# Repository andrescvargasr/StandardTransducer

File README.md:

# StandardTransducer

This repository is dedicated to the v0.2 of Standard Transducer.

## Electronics

The architecture for v0.2 is articulated around one central board powered by an ATmega32u4 MCU relying on ChibiOS/Nil RTOS with LoRa communication and external boards for interfacing to extra sensors, OLED screens and Bluetooth.

The main board comes with the following features:

- 4 ports for digital sensors under 1-wire communication protocol.

- 7 ports for 2 analog sensors with current source or voltage source and differential or single out (this ports was based in pressure sensor MPX53D and temperature sensor PT100).

- 1 port for OLED I2C screen.
- 1 port for 3.7 V battery source or 5 - 12 Vdc @ 1 A.
- 1 port for antenna extension (433 and 868 MHz).
- 1 port for test power source (Vcc).
- 1 port for change power source 3.3 Vdc / 5-12 Vdc.
- 1 port for 868 MHz antenna with SMA connector.
- 1 port for 868 MHz antenna with U.fl connector.
- 1 port for serial Bluetooth.
- 4 buttons for local configuration.
- 1 pad for soldering LoRa Ra-1 (do not include if RN2483 is part of the design).
- 1 pad for soldering LoRa RN2483 (do not include if Ra-01 is part of the design).

There are already a few external extra modules:

~~- OLED I2C slave.~~

~~- pH & Conductommetry regulation I2C slave, also works as a stand alone (in development phase)~~
~~

~~- Pressure analog sensor.~~

~~- Temperature analog sensor.~~

~~- gas flux and mix control with analogic valves, also works as a stand alone (in development phase).~~

References:

-https://www.arduino.cc/en/Main/ArduinoBoardLeonardo.

-https://github.com/greiman/ChNil.

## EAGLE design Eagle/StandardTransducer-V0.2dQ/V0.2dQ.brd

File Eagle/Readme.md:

The main board comes with the following features:

- 3 pads with 3 ports for digital sensors under 1-wire communication protocol.

Port | Name | Description
---|----|---------------------------------------------------------------------------------
1 | Vsensors | Digital Voltage source for one-wire sensors.
2 | One-wire | Digital output of sensors.
3 | GND | Ground for digital sensors.

- 1 connector with 2x5 ports for 2 analog sensors with current source or voltage source, differential or single out (this ports was based in pressure sensor MPX53D and temperature sensor PT100) and one-wire sensors.

Port | Name | Sensor Number | Description
---|----|-------------------------------|---------------------------------------------------------------------------------
1 | D+3V3 |  | Voltage source for sensor 1.
2 | AGND |  | Analog ground for sensor 1 and voltage source.
3 | Vout+ | 1 | Positive differential voltage output of sensor 1.
4 | Vout- | 1 | Negative Differential voltage output of sensor 1.
5 | Iexc |  | Current source for sensor 2.
6 | AGND |  | Analog ground for sensor 2 and current source.
7 | Vanalog | 2 | Analog voltage output of sensor 2.
8 | GND |  | Ground for different digital sensors connect in sensor 3.
9 | Vsensors | | Digital Voltage source for one-wire sensors.
10 | One-wire | 3 | Digital output of sensors in port 10.

- 1 connector with 4 ports for OLED I2C screen.

Port | Name | Description
---|----|---------------------------------------------------------------------------------
1 | SDA | Serial Data.
2 | SCL | Serial Clock.
3 | LCDVCC | Voltage source.
4 | GND | Ground.

- 1 connector with 3 ports for 3.7 V battery source or 5 - 12 Vdc @ 1 A.

Port | Name | Description
---|----|---------------------------------------------------------------------------------
1 | Vdd | 5 - 12 V @ 1 A voltage source.
2 | +3V3 | Battery source.
3 | GND | Ground.

- 1 port for antenna extension (433 and 868 MHz).
- 1 port for test power source (Vcc).
- 1 jumper for change power source 3.3 Vdc to 5-12 Vdc.
- 1 port for 868 MHz antenna with SMA connector.
- 1 port for 868 MHz antenna with U.fl connector.
- 1 connector with 4 ports for serial Bluetooth.

Port | Name | Description
---|----|---------------------------------------------------------------------------------
1 | D+3V3 | Voltage source.
2 | TX2 | Transmission port for slave.
3 | RX2 | Reception port for slave.
4 | GND | Ground.

- 4 buttons for local configuration.
- 1 pad for soldering LoRa Ra-1 (do not include if RN2483 is part of the design).
- 1 pad for soldering LoRa RN2483 (do not include if Ra-01 is part of the design).

References:

- https://www.luisllamas.es/temperatura-liquidos-arduino-ds18b20/
- https://www.nxp.com/docs/en/data-sheet/MPX53.pdf
- https://www.acromag.com/sites/default/files/RTD_Temperature_Measurement_917A.pdf
- https://learn.adafruit.com/monochrome-oled-breakouts
- https://hetpro-store.com/TUTORIALES/bluetooth-hc-06-app-arduino/
- http://www.abatek.com/designguide/04Electrical.html
- https://www.arduino.cc/en/Main/ArduinoBoardLeonardo

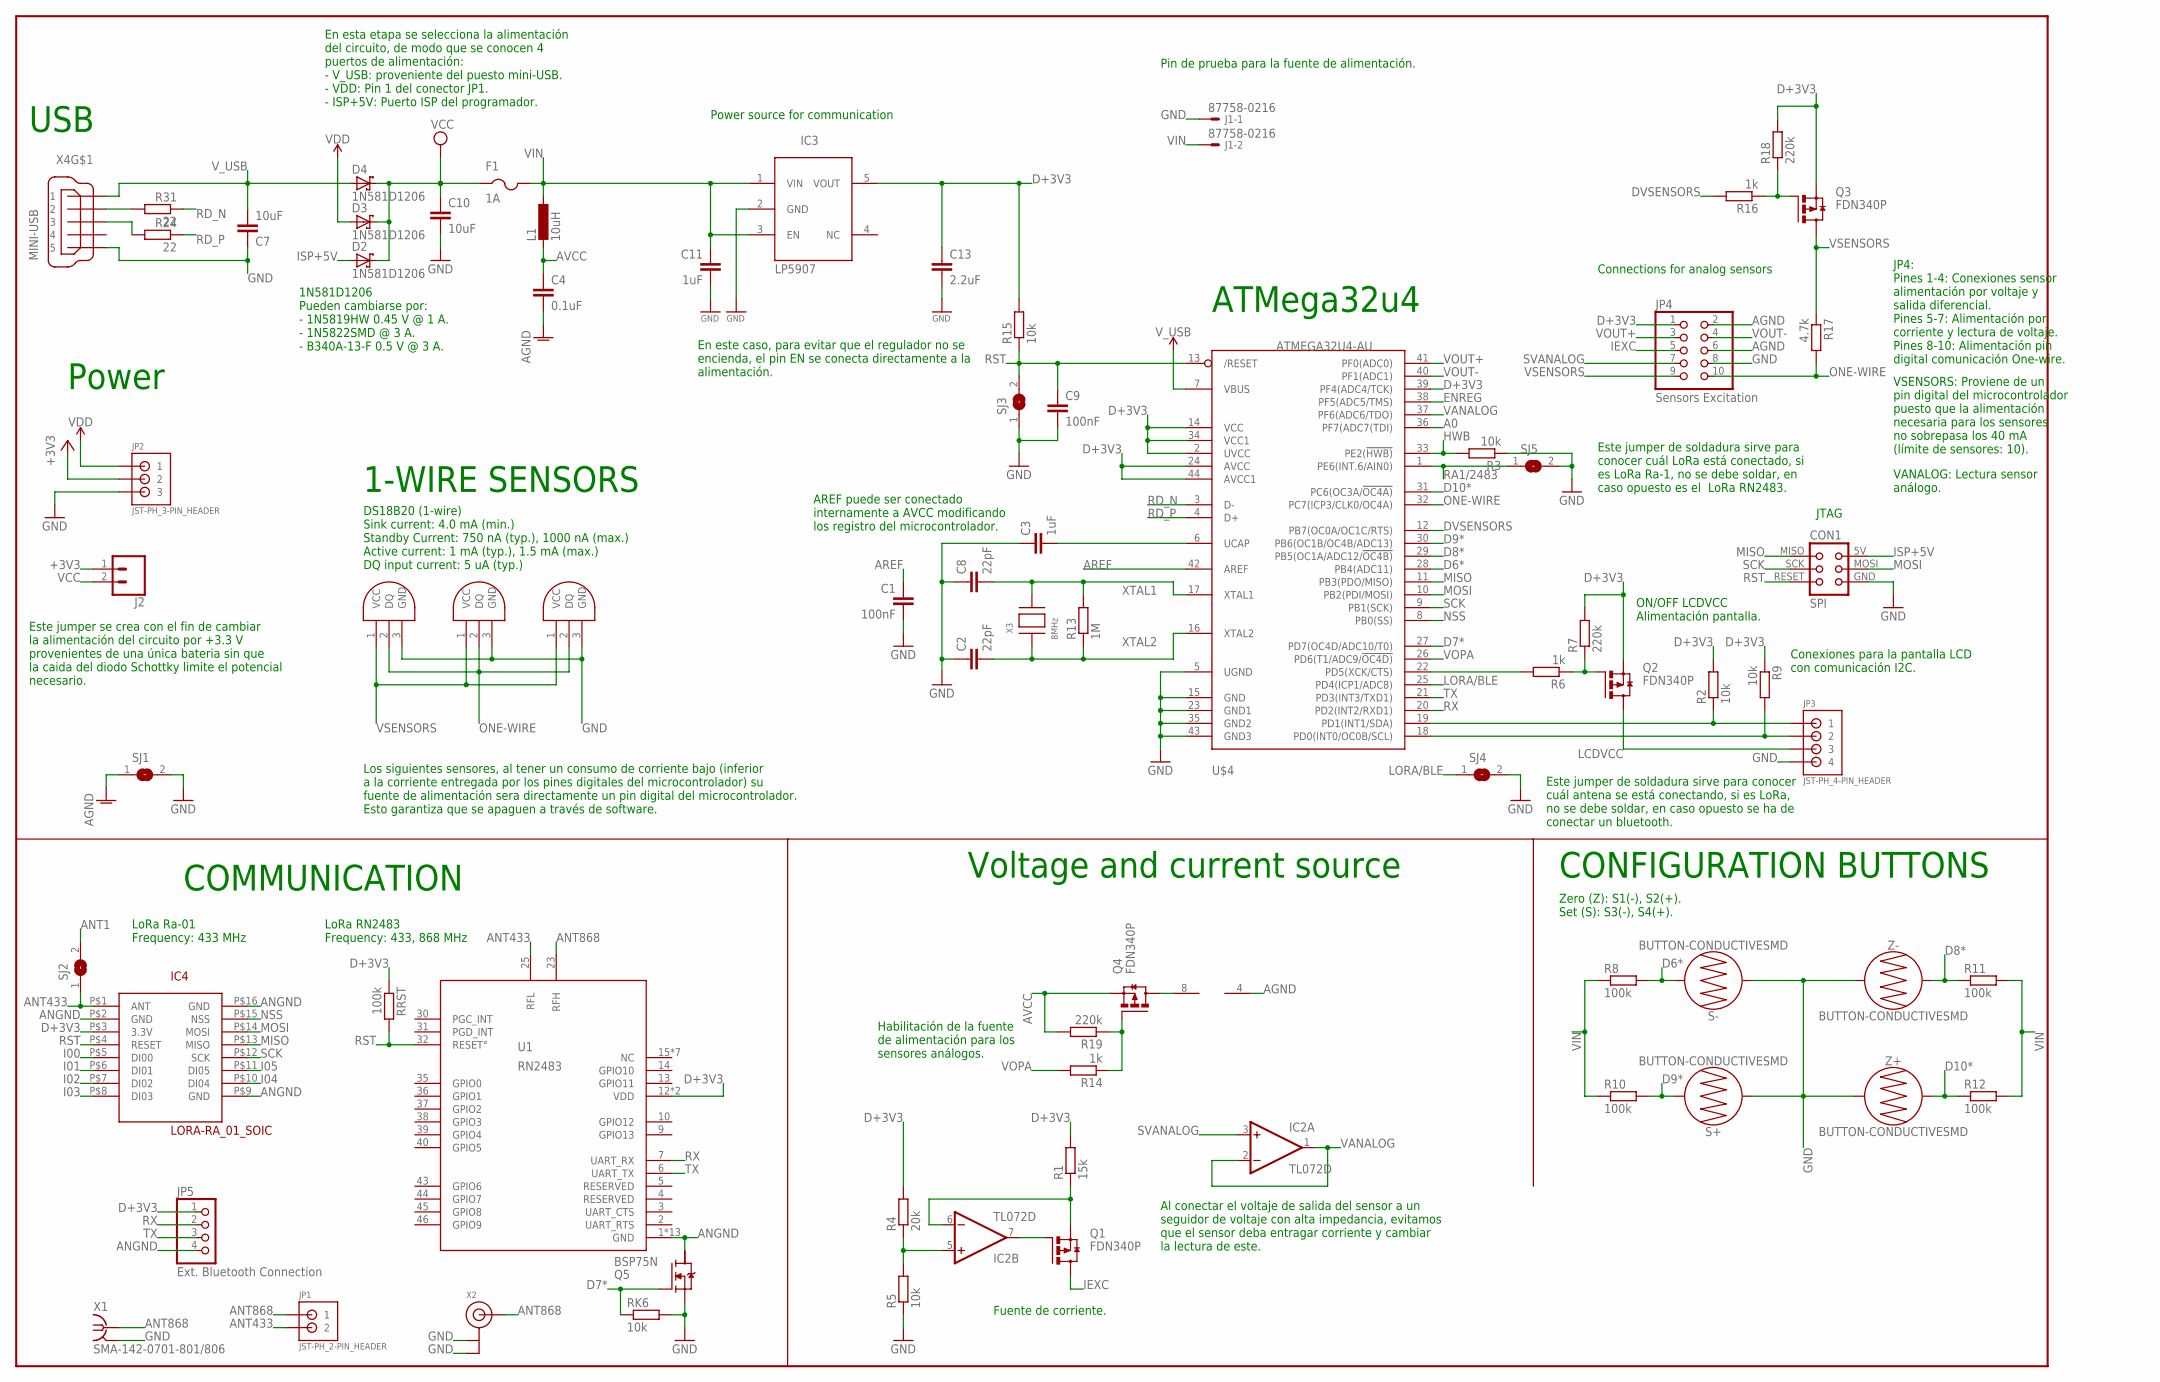
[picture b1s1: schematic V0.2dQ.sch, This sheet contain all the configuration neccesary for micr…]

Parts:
C1, C9: 100nF; C0805
C2, C8: 22pF; C0805
C3, C11: 1uF; C0805
C4: 0.1uF; C0805
C7: 10uF; C0805
C10: 10uF; C1206
C13: 2.2uF; C0805
CON1: SPI; TC2030-MCP-NL
D2, D3, D4: 1N581D1206; LED-1206
F1: 1A; 1812
IC2: TL072D; SO08
IC3: LP5907; SOT23-5L
IC4: LORA-RA_01_SOIC; LORA-RA_01
J1: 87758-0216
J2: CONN_02; 1X02
JP1: JST-PH_2-PIN_HEADER; JST_B2B-PH_HEADER
JP2: JST-PH_3-PIN_HEADER; JST_B3B-PH_HEADER
JP3: JST-PH_4-PIN_HEADER; JST_B4B-PH_HEADER
JP4: Sensors Excitation; 2X05/90
JP5: Ext. Bluetooth Connection; 1X04
L1: 10uH; L1812
Q1, Q2, Q3, Q4: FDN340P; SUPER-SOT3
Q5: BSP75N; PG-SOT223-4
R1: 15k; R0805
R2, R3, R5, R9: 10k; R0805
R4: 20k; R0805
R6, R14, R16: 1k; R0805
R7, R18, R19: 220k; R0805
R8, R10, R11, R12: 100k; R0805
R13: 1M; R0805
R15: 10k; M0805
R17: 4.7k; R0805
R24, R31: 22; R0805
RK6: 10k; M0805
RRST: 100k; R0805
S+: BUTTON-CONDUCTIVESMD; BUTTON-CONDUCTIVE
S-: BUTTON-CONDUCTIVESMD; BUTTON-CONDUCTIVE
SJ1, SJ2, SJ3, SJ4, SJ5: SJ
U1: RN2483
U$4: ATMEGA32U4-AU; TQFP44
U$5, U$6, U$9: DS18B20_PINS; 3PINS_SMALL
X1: SMA-142-0701-801/806; J502-ND-142-0701-801/806
X2: ANTENNA_U.FL; U.FL
X3: 8MHz; NX6035
X4: MINI-USB; 32005-201
Z+: BUTTON-CONDUCTIVESMD; BUTTON-CONDUCTIVE
Z-: BUTTON-CONDUCTIVESMD; BUTTON-CONDUCTIVE

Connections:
A0: U$4.36 (PF7(ADC7(TDI))
AGND: C4.2, IC2.4 (V-), JP4.2, JP4.6, SJ1.1
ANGND: IC4.P$2 (GND), IC4.P$9 (GND), IC4.P$16 (GND), JP5.4, Q5.2 (D), U1.1 (GND), U1.8 (GND), U1.11 (GND), U1.20 (GND), U1.21 (GND), U1.22 (GND), U1.24 (GND), U1.26 (GND), U1.27 (GND), U1.28 (GND), U1.33 (GND), U1.41 (GND), U1.47 (GND)
ANT1: SJ2.2
ANT433: IC4.P$1 (ANT), JP1.P2 (2), SJ2.1, U1.25 (RFL)
ANT868: JP1.P1 (1), U1.23 (RFH), X1.1, X2.3 (SIGNAL)
AREF: C1.1, U$4.42 (AREF)
AVCC: C4.1, L1.2, Q4.2 (S), R19.2
AVCCOPA: IC2.8 (V+), Q4.3 (D)
D6*: R8.2, S-.2, U$4.28 (PB4(ADC11))
D7*: Q5.1 (G), RK6.1, U$4.27 (PD7(OC4D/ADC10/T0))
D8*: R11.1, U$4.29 (PB5(OC1A/ADC12/!OC4B)), Z-.2
D9*: R10.2, S+.2, U$4.30 (PB6(OC1B/OC4B/ADC13))
D10*: R12.1, U$4.31 (PC6(OC3A/!OC4A)), Z+.2
D+3V3: C13.1, IC3.5 (VOUT), IC4.P$3 (3.3V), JP4.1, JP5.1, Q2.2 (S), Q3.2 (S), R1.2, R2.2, R4.2, R7.2, R9.1, R15.2, R18.2, RRST.1, U1.12 (VDD), U1.34 (VDD), U$4.2 (UVCC), U$4.14 (VCC), U$4.24 (AVCC), U$4.34 (VCC1), U$4.39 (PF4(ADC4/TCK)), U$4.44 (AVCC1)
D+USB: R24.2, X4.3
D-USB: R31.2, X4.2
DVSENSORS: R16.2, U$4.12 (PB7(OC0A/OC1C/RTS))
ENLCD: R6.2, U$4.22 (PD5(XCK/CTS))
ENREG: U$4.38 (PF5(ADC5/TMS))
GND: C1.2, C2.1, C3.1, C7.1, C8.1, C9.2, C10.2, C11.2, C13.2, CON1.GND, IC3.2 (GND), J1.1, JP2.P3 (3), JP3.P4 (4), JP4.8, Q5.3 (S), R3.1, R5.1, RK6.2, S+.1, S-.1, SJ1.2, SJ3.1, SJ4.2, SJ5.2, U$4.5 (UGND), U$4.15 (GND), U$4.23 (GND1), U$4.35 (GND2), U$4.43 (GND3), U$5.3 (GND), U$6.3 (GND), U$9.3 (GND), X1.G@1 (2), X1.G@2 (2), X1.G@3 (2), X1.G@4 (2), X2.1 (GND), X2.2 (GND), X4.5, Z+.1, Z-.1; also elsewhere on the board
HWB: R3.2, U$4.33 (PE2(!HWB))
I00: IC4.P$5 (DI00)
I01: IC4.P$6 (DI01)
I02: IC4.P$7 (DI02)
I03: IC4.P$8 (DI03)
I04: IC4.P$10 (DI04)
I05: IC4.P$11 (DI05)
IEXC: JP4.5, Q1.3 (D)
ISP+5V: CON1.5V (VCC), D2.A
LCDVCC: JP3.P3 (3), Q2.3 (D)
LORA/BLE: SJ4.1, U$4.25 (PD4(ICP1/ADC8))
MISO: CON1.MISO, IC4.P$13 (MISO), U$4.11 (PB3(PDO/MISO))
MOSI: CON1.MOSI, IC4.P$14 (MOSI), U$4.10 (PB2(PDI/MOSI))
unnamed: IC2.7 (OUT), Q1.1 (G)
unnamed: Q4.1 (G), R14.1, R19.1
unnamed: IC2.5 (+IN), R4.1, R5.2
unnamed: IC2.6 (-IN), Q1.2 (S), R1.1
unnamed: Q2.1 (G), R6.1, R7.1
unnamed: Q3.1 (G), R16.1, R18.1
NSS: IC4.P$15 (NSS), U$4.8 (PB0(SS))
unnamed: D3.A, JP2.P1 (1)
unnamed: J2.1, JP2.P2 (2)
ONE-WIRE: JP4.10, R17.2, U$4.32 (PC7(ICP3/CLK0/OC4A)), U$5.2 (DQ), U$6.2 (DQ), U$9.2 (DQ)
RA1/2483: SJ5.1, U$4.1 (PE6(INT.6/AIN0))
RD_N: R31.1, U$4.3 (D-)
RD_P: R24.1, U$4.4 (D+)
RST: C9.1, CON1.RESET, IC4.P$4 (RESET), R15.1, RRST.2, SJ3.2, U1.32 (RESET°), U$4.13 (/RESET)
RX: JP5.2, U1.7 (UART_RX), U$4.20 (PD2(INT2/RXD1))
SCK: CON1.SCK, IC4.P$12 (SCK), U$4.9 (PB1(SCK))
SCL: JP3.P2 (2), R9.2, U$4.18 (PD0(INT0/OC0B/SCL))
SDA: JP3.P1 (1), R2.1, U$4.19 (PD1(INT1/SDA))
SVANALOG: IC2.3 (+IN), JP4.7
TX: JP5.3, U1.6 (UART_TX), U$4.21 (PD3(INT3/TXD1))
UCAP: C3.2, U$4.6 (UCAP)
VANALOG: IC2.1 (OUT), IC2.2 (-IN), U$4.37 (PF6(ADC6/TDO))
VOPA: R14.2, U$4.26 (PD6(T1/ADC9/!OC4D))
VOUT+: JP4.3, U$4.41 (PF0(ADC0))
VOUT-: JP4.4, U$4.40 (PF1(ADC1))
VSENSORS: JP4.9, Q3.3 (D), R17.1, U$5.1 (VCC), U$6.1 (VCC), U$9.1 (VCC)
V_USB: C7.2, D4.A, U$4.7 (VBUS), X4.1
XTAL1: C8.2, R13.2, U$4.17 (XTAL1), X3.P$2
XTAL2: C2.2, R13.1, U$4.16 (XTAL2), X3.P$1

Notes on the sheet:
ATMega32u4
LoRa Ra-01 Frequency: 433 MHz
LoRa RN2483 Frequency: 433, 868 MHz
VSENSORS: Proviene de un pin digital del microcontrolador puesto que la alimentación necesaria para los sensores no sobrepasa los 40 mA (límite de sensores: 10).
VANALOG: Lectura sensor análogo.
Connections for analog sensors
JP4: Pines 1-4: Conexiones sensor alimentación por voltaje y salida diferencial. Pines 5-7: Alimentación por corriente y lectura de voltaje. Pines 8-10: Alimentación pin digital comunicación One-wire.
JTAG
ON/OFF LCDVCC Alimentación pantalla.
Conexiones para la pantalla LCD con comunicación I2C.
Voltage and current source
AREF puede ser conectado internamente a AVCC modificando los registro del microcontrolador.
Este jumper de soldadura sirve para conocer cuál antena se está conectando, si es LoRa, no se debe soldar, en caso opuesto se ha de conectar un bluetooth.
Este jumper de soldadura sirve para conocer cuál LoRa está conectado, si es LoRa Ra-1, no se debe soldar, en caso opuesto es el LoRa RN2483.
Al conectar el voltaje de salida del sensor a un seguidor de voltaje con alta impedancia, evitamos que el sensor deba entragar corriente y cambiar la lectura de este.
COMMUNICATION
Habilitación de la fuente de alimentación para los sensores análogos.
Fuente de corriente.
CONFIGURATION BUTTONS
Zero (Z): S1(-), S2(+). Set (S): S3(-), S4(+).
DS18B20 (1-wire) Sink current: 4.0 mA (min.) Standby Current: 750 nA (typ.), 1000 nA (max.) Active current: 1 mA (typ.), 1.5 mA (max.) DQ input current: 5 uA (typ.)
Los siguientes sensores, al tener un consumo de corriente bajo (inferior a la corriente entregada por los pines digitales del microcontrolador) su fuente de alimentación sera directamente un pin digital del microcontrolador. Esto garantiza que se apaguen a través de software.
1-WIRE SENSORS
Pin de prueba para la fuente de alimentación.
USB
1N581D1206 Pueden cambiarse por: - 1N5819HW 0.45 V @ 1 A. - 1N5822SMD @ 3 A. - B340A-13-F 0.5 V @ 3 A.
En esta etapa se selecciona la alimentación del circuito, de modo que se conocen 4 puertos de alimentación: - V_USB: proveniente del puesto mini-USB. - VDD: Pin 1 del conector JP1. - ISP+5V: Puerto ISP del programador.
Power source for communication
En este caso, para evitar que el regulador no se encienda, el pin EN se conecta directamente a la alimentación.
Power
Este jumper se crea con el fin de cambiar la alimentación del circuito por +3.3 V provenientes de una única bateria sin que la caida del diodo Schottky limite el potencial necesario.

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
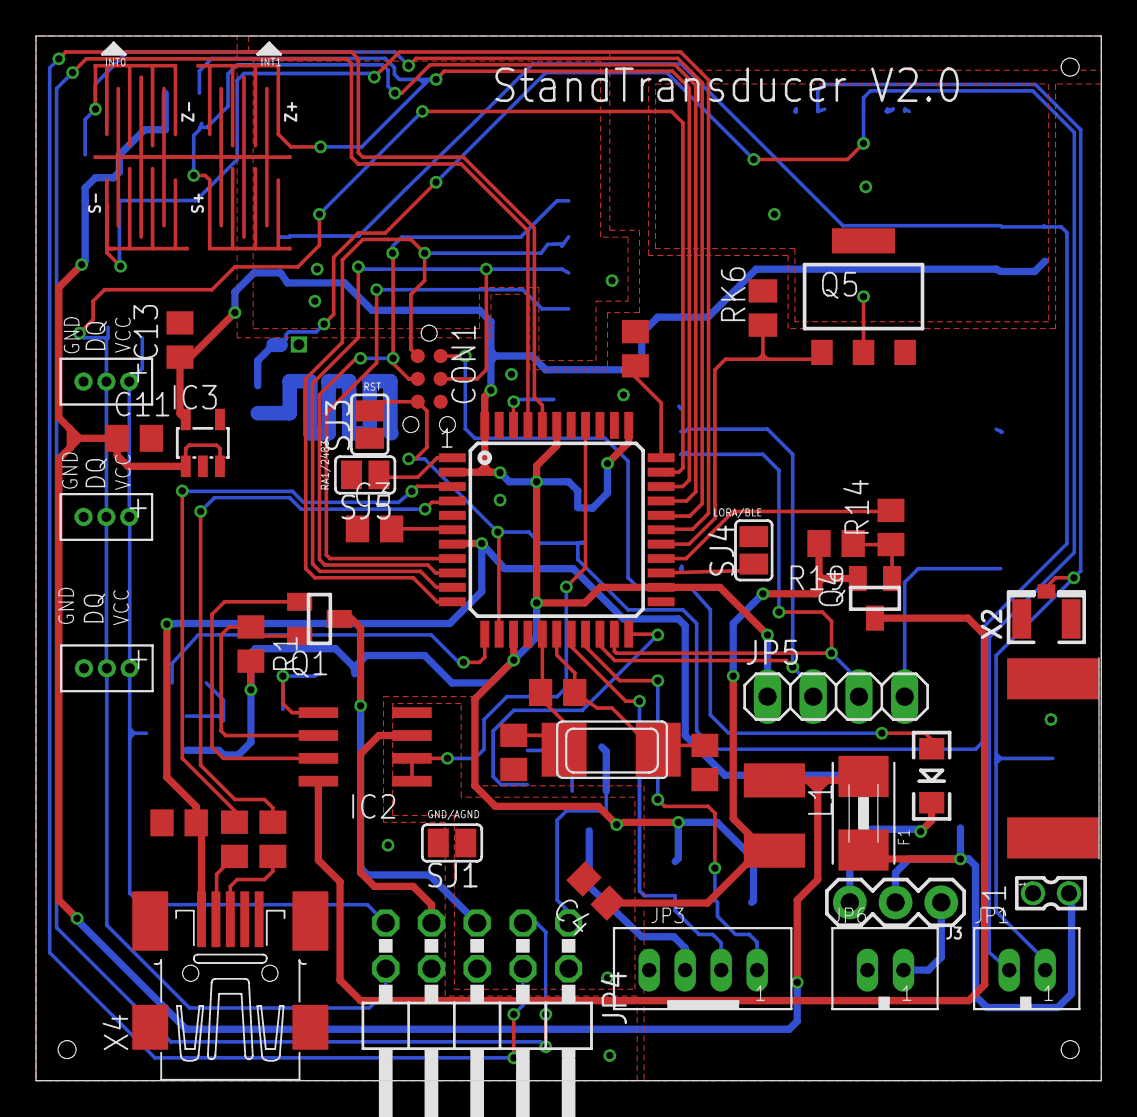
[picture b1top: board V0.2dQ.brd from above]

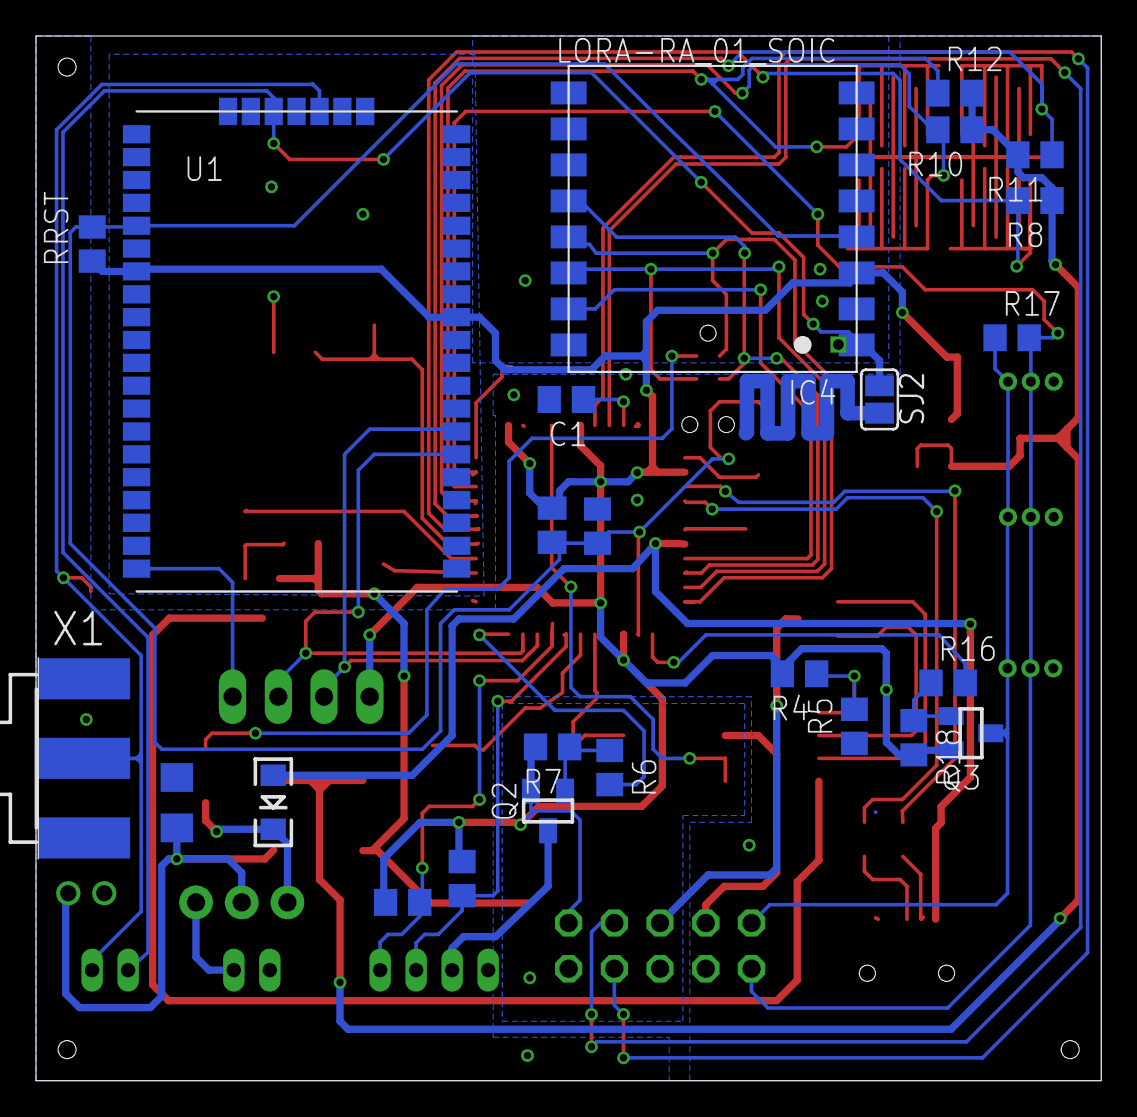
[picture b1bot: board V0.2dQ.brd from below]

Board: 2 copper layers, 59.2 x 58.0 mm, 71 parts (25 on the bottom side), 56 nets.

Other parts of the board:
J3: 455-1750-1-ND; 1X03
JP6: JST-PH_2-PIN_HEADER; JST_B2B-PH_HEADER

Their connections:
GND: JP6.P2; also elsewhere on the board
VDD: J3.1, JP6.P1

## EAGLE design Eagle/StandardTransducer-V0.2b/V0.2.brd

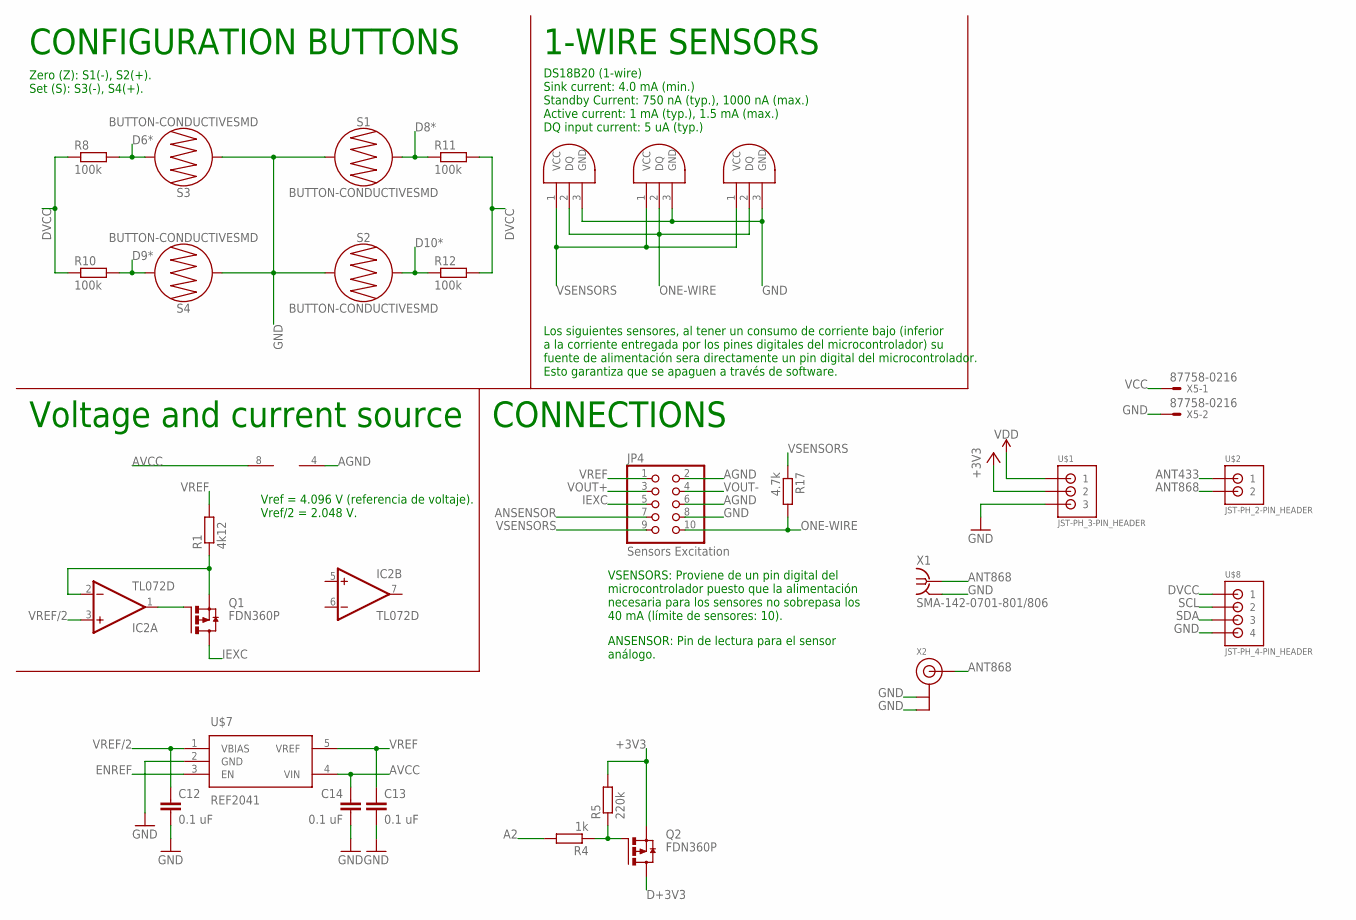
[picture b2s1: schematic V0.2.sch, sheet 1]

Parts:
C12, C13, C14: 0.1 uF; C0805
IC2: TL072D; SO08
JP4: Sensors Excitation; 2X05/90
Q1, Q2: FDN360P; SUPER-SOT3
R1: 4k12; R0805
R4: 1k; R0805
R5: 220k; R0805
R8, R10, R11, R12: 100k; R0805
R17: 4.7k; R0805
S1, S2, S3, S4: BUTTON-CONDUCTIVESMD; BUTTON-CONDUCTIVE
U$1: JST-PH_3-PIN_HEADER; JST_B3B-PH_HEADER
U$2: JST-PH_2-PIN_HEADER; JST_B2B-PH_HEADER
U$5, U$6, U$9: DS18B20_PINS; 3PINS_SMALL
U$7: REF2041; SOT(5)
U$8: JST-PH_4-PIN_HEADER; JST_B4B-PH_HEADER
X1: SMA-142-0701-801/806; J502-ND-142-0701-801/806
X2: ANTENNA_U.FL; U.FL
X5: 87758-0216

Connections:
+3V3: Q2.2 (S), R5.2, U$1.P2 (2); also elsewhere on the board
A2: R4.2; also elsewhere on the board
AGND: IC2.4 (V-), JP4.2, JP4.6; also elsewhere on the board
ANSENSOR: JP4.7; also elsewhere on the board
ANT433: U$2.P1 (1); also elsewhere on the board
ANT868: U$2.P2 (2), X1.1, X2.3 (SIGNAL); also elsewhere on the board
AVCC: C14.1, IC2.8 (V+), U$7.4 (VIN); also elsewhere on the board
D6*: R8.2, S3.2; also elsewhere on the board
D8*: R11.1, S1.2; also elsewhere on the board
D9*: R10.2, S4.2; also elsewhere on the board
D10*: R12.1, S2.2; also elsewhere on the board
D+3V3: Q2.3 (D); also elsewhere on the board
DVCC: R8.1, R10.1, R11.2, R12.2, U$8.P1 (1); also elsewhere on the board
ENREF: U$7.3 (EN); also elsewhere on the board
GND: C12.2, C13.2, C14.2, JP4.8, S1.1, S2.1, S3.1, S4.1, U$1.P3 (3), U$5.3 (GND), U$6.3 (GND), U$7.2 (GND), U$8.P4 (4), U$9.3 (GND), X1.G@1 (2), X1.G@2 (2), X1.G@3 (2), X1.G@4 (2), X2.1 (GND), X2.2 (GND), X5.2; also elsewhere on the board
IEXC: JP4.5, Q1.3 (D)
unnamed: IC2.1 (OUT), Q1.1 (G)
unnamed: Q2.1 (G), R4.1, R5.1
unnamed: IC2.2 (-IN), Q1.2 (S), R1.1
ONE-WIRE: JP4.10, R17.2, U$5.2 (DQ), U$6.2 (DQ), U$9.2 (DQ); also elsewhere on the board
SCL: U$8.P2 (2); also elsewhere on the board
SDA: U$8.P3 (3); also elsewhere on the board
VCC: X5.1; also elsewhere on the board
VDD: U$1.P1 (1); also elsewhere on the board
VOUT+: JP4.3; also elsewhere on the board
VOUT-: JP4.4; also elsewhere on the board
VREF: C13.1, JP4.1, R1.2, U$7.5 (VREF); also elsewhere on the board
VREF/2: C12.1, IC2.3 (+IN), U$7.1 (VBIAS)
VSENSORS: JP4.9, R17.1, U$5.1 (VCC), U$6.1 (VCC), U$9.1 (VCC); also elsewhere on the board

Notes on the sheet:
Voltage and current source
CONFIGURATION BUTTONS
Zero (Z): S1(-), S2(+). Set (S): S3(-), S4(+).
DS18B20 (1-wire) Sink current: 4.0 mA (min.) Standby Current: 750 nA (typ.), 1000 nA (max.) Active current: 1 mA (typ.), 1.5 mA (max.) DQ input current: 5 uA (typ.)
Los siguientes sensores, al tener un consumo de corriente bajo (inferior a la corriente entregada por los pines digitales del microcontrolador) su fuente de alimentación sera directamente un pin digital del microcontrolador. Esto garantiza que se apaguen a través de software.
1-WIRE SENSORS
VSENSORS: Proviene de un pin digital del microcontrolador puesto que la alimentación necesaria para los sensores no sobrepasa los 40 mA (límite de sensores: 10).
ANSENSOR: Pin de lectura para el sensor análogo.
CONNECTIONS
Vref = 4.096 V (referencia de voltaje). Vref/2 = 2.048 V.

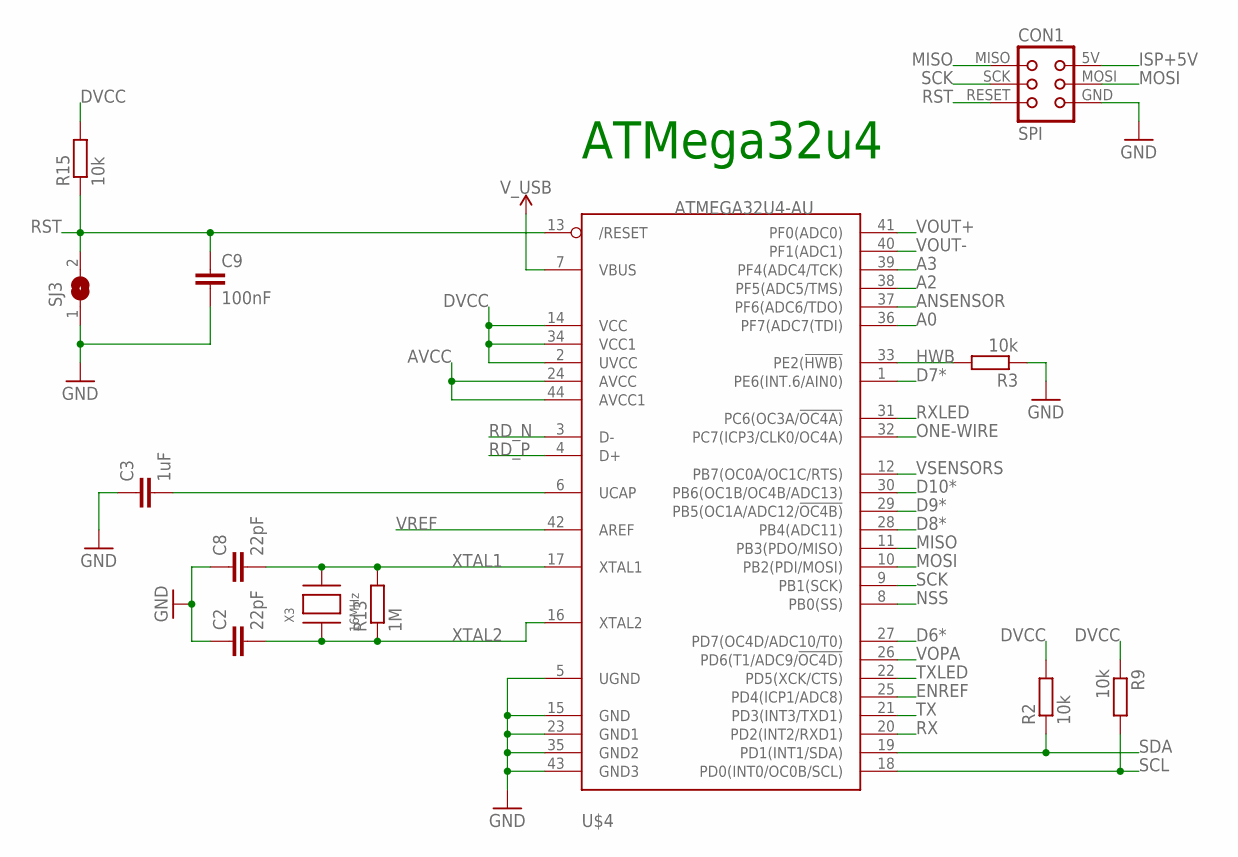
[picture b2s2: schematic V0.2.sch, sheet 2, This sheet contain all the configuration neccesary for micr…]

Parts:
C2, C8: 22pF; C1206
C3: 1uF; C1206
C9: 100nF; C1206
CON1: SPI; TC2030-MCP-NL
R2, R3, R9: 10k; M1206
R13: 1M; R1206
R15: 10k; M0805
SJ3: SJ
U$4: ATMEGA32U4-AU; TQFP44
X3: 16MHz; NX6035

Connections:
A0: U$4.36 (PF7(ADC7(TDI))
A2: U$4.38 (PF5(ADC5/TMS)); also elsewhere on the board
A3: U$4.39 (PF4(ADC4/TCK))
ANSENSOR: U$4.37 (PF6(ADC6/TDO)); also elsewhere on the board
AVCC: U$4.24 (AVCC), U$4.44 (AVCC1); also elsewhere on the board
D6*: U$4.27 (PD7(OC4D/ADC10/T0)); also elsewhere on the board
D7*: U$4.1 (PE6(INT.6/AIN0))
D8*: U$4.28 (PB4(ADC11)); also elsewhere on the board
D9*: U$4.29 (PB5(OC1A/ADC12/!OC4B)); also elsewhere on the board
D10*: U$4.30 (PB6(OC1B/OC4B/ADC13)); also elsewhere on the board
DVCC: R2.2, R9.1, R15.2, U$4.2 (UVCC), U$4.14 (VCC), U$4.34 (VCC1); also elsewhere on the board
ENREF: U$4.25 (PD4(ICP1/ADC8)); also elsewhere on the board
GND: C2.1, C3.1, C8.1, C9.2, CON1.GND, R3.1, SJ3.1, U$4.5 (UGND), U$4.15 (GND), U$4.23 (GND1), U$4.35 (GND2), U$4.43 (GND3); also elsewhere on the board
HWB: R3.2, U$4.33 (PE2(!HWB))
ISP+5V: CON1.5V (VCC); also elsewhere on the board
MISO: CON1.MISO, U$4.11 (PB3(PDO/MISO)); also elsewhere on the board
MOSI: CON1.MOSI, U$4.10 (PB2(PDI/MOSI)); also elsewhere on the board
NSS: U$4.8 (PB0(SS)); also elsewhere on the board
ONE-WIRE: U$4.32 (PC7(ICP3/CLK0/OC4A)); also elsewhere on the board
RD_N: U$4.3 (D-); also elsewhere on the board
RD_P: U$4.4 (D+); also elsewhere on the board
RST: C9.1, CON1.RESET, R15.1, SJ3.2, U$4.13 (/RESET); also elsewhere on the board
RX: U$4.20 (PD2(INT2/RXD1)); also elsewhere on the board
RXLED: U$4.31 (PC6(OC3A/!OC4A))
SCK: CON1.SCK, U$4.9 (PB1(SCK)); also elsewhere on the board
SCL: R9.2, U$4.18 (PD0(INT0/OC0B/SCL)); also elsewhere on the board
SDA: R2.1, U$4.19 (PD1(INT1/SDA)); also elsewhere on the board
TX: U$4.21 (PD3(INT3/TXD1)); also elsewhere on the board
TXLED: U$4.22 (PD5(XCK/CTS))
UCAP: C3.2, U$4.6 (UCAP)
VOPA: U$4.26 (PD6(T1/ADC9/!OC4D))
VOUT+: U$4.41 (PF0(ADC0)); also elsewhere on the board
VOUT-: U$4.40 (PF1(ADC1)); also elsewhere on the board
VREF: U$4.42 (AREF); also elsewhere on the board
VSENSORS: U$4.12 (PB7(OC0A/OC1C/RTS)); also elsewhere on the board
V_USB: U$4.7 (VBUS); also elsewhere on the board
XTAL1: C8.2, R13.2, U$4.17 (XTAL1), X3.P$2
XTAL2: C2.2, R13.1, U$4.16 (XTAL2), X3.P$1

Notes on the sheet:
ATMega32u4

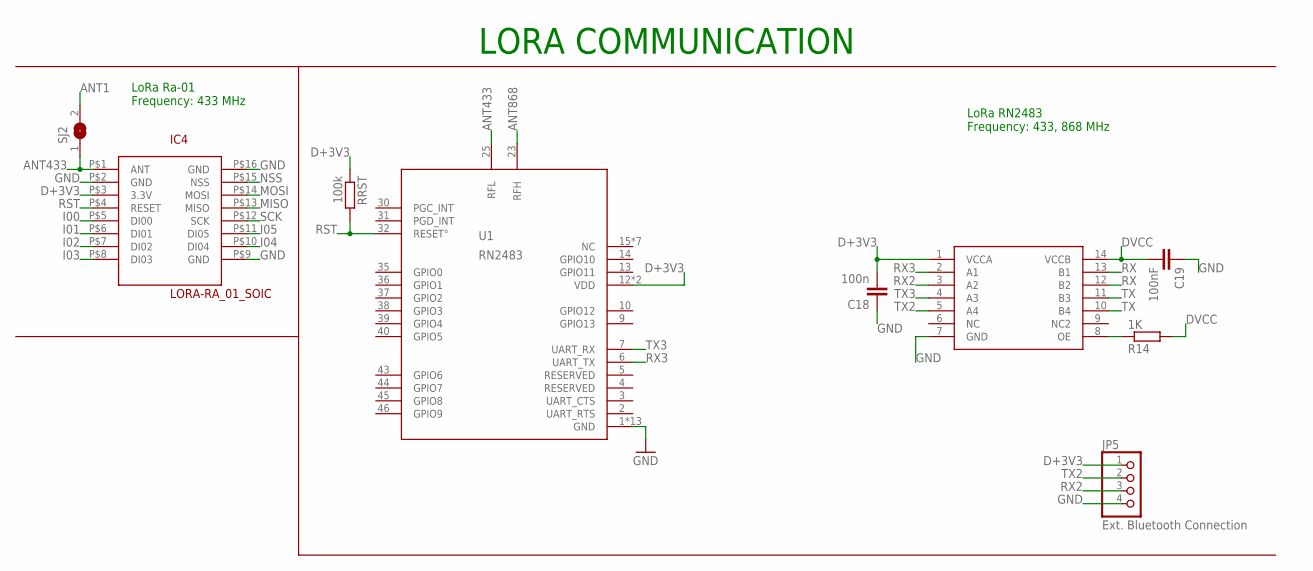
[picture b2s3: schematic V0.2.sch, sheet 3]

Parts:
C18: 100n; C1206
C19: 100nF; C1206
IC4: LORA-RA_01_SOIC; LORA-RA_01
JP5: Ext. Bluetooth Connection; 1X04
R14: 1K; R0805
RRST: 100k; R0805
SJ2: SJ
U1: RN2483
U$3: TXB0104; SO14

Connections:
ANT1: SJ2.2
ANT433: IC4.P$1 (ANT), SJ2.1, U1.25 (RFL); also elsewhere on the board
ANT868: U1.23 (RFH); also elsewhere on the board
D+3V3: C18.2, IC4.P$3 (3.3V), JP5.1, RRST.1, U1.12 (VDD), U1.34 (VDD), U$3.1 (VCCA); also elsewhere on the board
DVCC: C19.2, R14.2, U$3.14 (VCCB); also elsewhere on the board
GND: C18.1, C19.1, IC4.P$2 (GND), IC4.P$9 (GND), IC4.P$16 (GND), JP5.4, U1.1 (GND), U1.8 (GND), U1.11 (GND), U1.20 (GND), U1.21 (GND), U1.22 (GND), U1.24 (GND), U1.26 (GND), U1.27 (GND), U1.28 (GND), U1.33 (GND), U1.41 (GND), U1.47 (GND), U$3.7 (GND); also elsewhere on the board
I00: IC4.P$5 (DI00)
I01: IC4.P$6 (DI01)
I02: IC4.P$7 (DI02)
I03: IC4.P$8 (DI03)
I04: IC4.P$10 (DI04)
I05: IC4.P$11 (DI05)
MISO: IC4.P$13 (MISO); also elsewhere on the board
MOSI: IC4.P$14 (MOSI); also elsewhere on the board
unnamed: R14.1, U$3.8 (OE)
NSS: IC4.P$15 (NSS); also elsewhere on the board
RST: IC4.P$4 (RESET), RRST.2, U1.32 (RESET°); also elsewhere on the board
RX: U$3.12 (B2), U$3.13 (B1); also elsewhere on the board
RX2: JP5.3, U$3.3 (A2)
RX3: U1.6 (UART_TX), U$3.2 (A1)
SCK: IC4.P$12 (SCK); also elsewhere on the board
TX: U$3.10 (B4), U$3.11 (B3); also elsewhere on the board
TX2: JP5.2, U$3.5 (A4)
TX3: U1.7 (UART_RX), U$3.4 (A3)

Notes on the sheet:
LoRa Ra-01 Frequency: 433 MHz
LORA COMMUNICATION
LoRa RN2483 Frequency: 433, 868 MHz

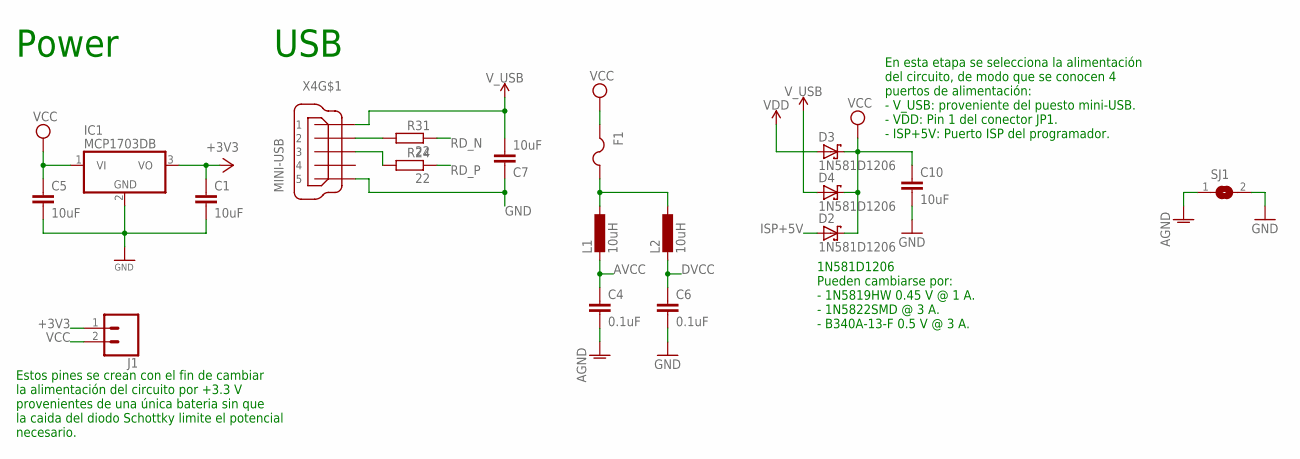
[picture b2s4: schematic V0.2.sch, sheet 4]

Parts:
C1, C5, C7, C10: 10uF; C1206
C4, C6: 0.1uF; C0805
D2, D3, D4: 1N581D1206; LED-1206
F1: PTCFUSE-1812; 1812
IC1: MCP1703DB; SOT223
J1: CONN_02; 1X02
L1, L2: 10uH; L1812
R24, R31: 22; R0805
SJ1: SJ
X4: MINI-USB; 32005-201

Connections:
+3V3: C1.1, IC1.3 (VO), J1.1; also elsewhere on the board
AGND: C4.2, SJ1.1; also elsewhere on the board
AVCC: C4.1, L1.2; also elsewhere on the board
D+USB: R24.2, X4.3
D-USB: R31.2, X4.2
DVCC: C6.1, L2.2; also elsewhere on the board
GND: C1.2, C5.2, C6.2, C7.1, C10.2, IC1.2 (GND), SJ1.2, X4.5; also elsewhere on the board
ISP+5V: D2.A; also elsewhere on the board
unnamed: F1.2, L1.1, L2.1
RD_N: R31.1; also elsewhere on the board
RD_P: R24.1; also elsewhere on the board
VCC: C5.1, C10.1, D2.C, D3.C, D4.C, F1.1, IC1.1 (VI), J1.2; also elsewhere on the board
VDD: D3.A; also elsewhere on the board
V_USB: C7.2, D4.A, X4.1; also elsewhere on the board

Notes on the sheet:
USB
Power
1N581D1206 Pueden cambiarse por: - 1N5819HW 0.45 V @ 1 A. - 1N5822SMD @ 3 A. - B340A-13-F 0.5 V @ 3 A.
En esta etapa se selecciona la alimentación del circuito, de modo que se conocen 4 puertos de alimentación: - V_USB: proveniente del puesto mini-USB. - VDD: Pin 1 del conector JP1. - ISP+5V: Puerto ISP del programador.
Estos pines se crean con el fin de cambiar la alimentación del circuito por +3.3 V provenientes de una única bateria sin que la caida del diodo Schottky limite el potencial necesario.

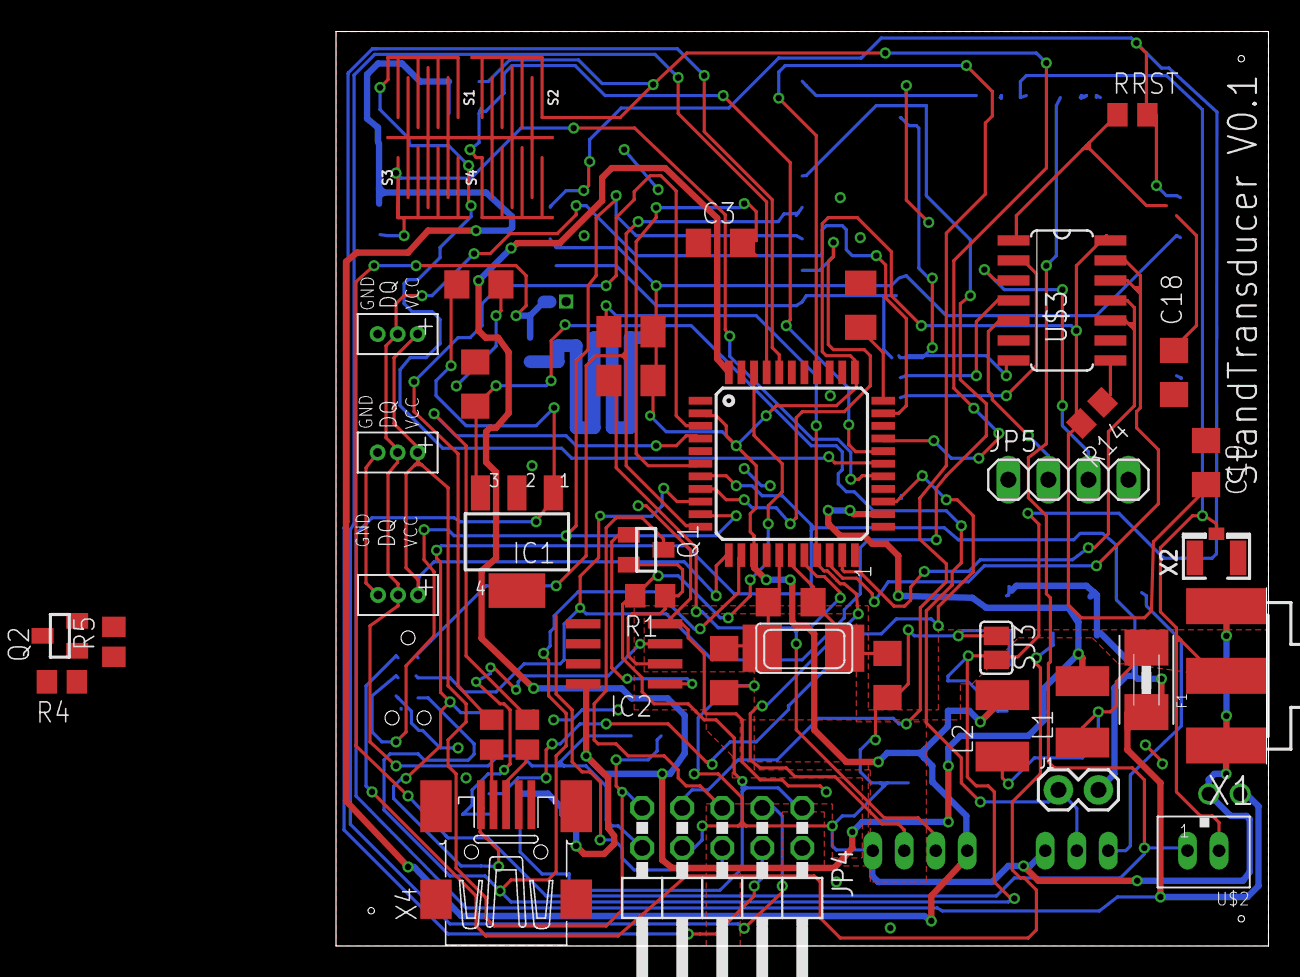
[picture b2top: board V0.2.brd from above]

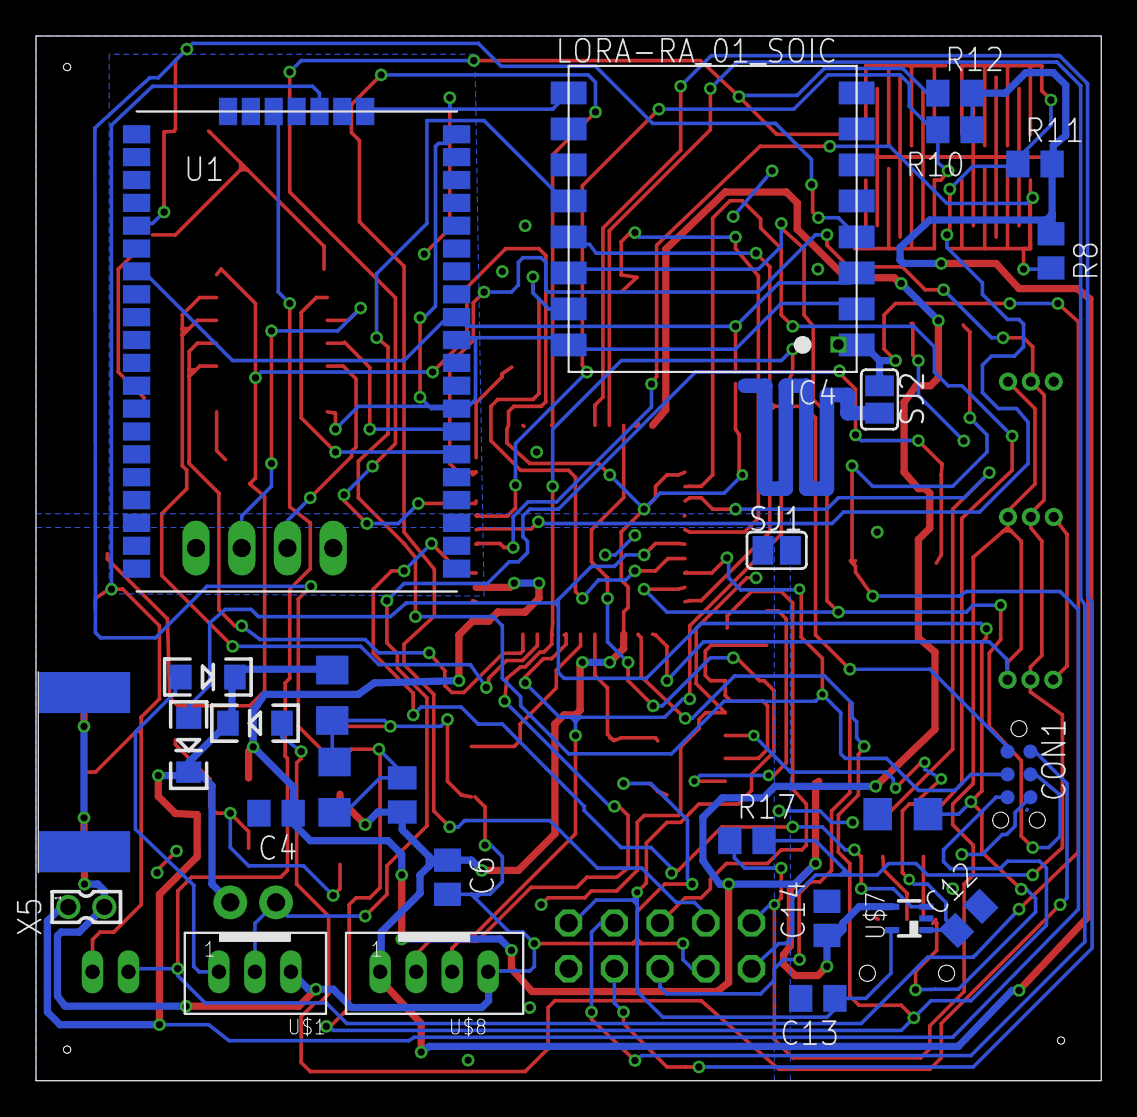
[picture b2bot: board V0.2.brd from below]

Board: 2 copper layers, 59.2 x 58.0 mm, 69 parts (26 on the bottom side), 52 nets.

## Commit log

2018-02-02 First commit
    Upload License and Readme files.
2018-02-23 Eagle design
    Eagle design, last version 0.2c
2018-02-24 Remove old versions and add gerber files
    Remove versions V0.1, V0.2, V0.2b and zip files with gerber with requirements from some manufacturers.
2018-02-24 Removes V0.2gerber
2018-02-24 Create Readme for Eagle folder and update Readme for root.
    New Readme into Eagle folder was created and update Readme in root was made.
2018-02-26 New version without TXB0104
    Remove TXB0104 to translate TTL signal to 3.3 V signals. It's no neccesary.
2018-02-28 New version of 02.dQ
2018-02-28 New version of 0.2dQ
2018-02-28 Change width to 16 mil for SVANALOG route.
2018-02-28 Changes width for VCCOPA and SVANALOG
2018-02-28 EN pin of LP298SX is connect to VIN pin.
    - Delete sheets 2, 3 and 4 and paste all the components and connections to sheet 1.
    - EN pin is connect to VIN pin for LP298SX to ensure that microcontroller have power source.
    - Change width for all route of D+3V3.
    - Change conections for TL072D to minimize route and vias for SVANALOG.
2018-03-01 Update ICs and routes.
    Changes made:
    - BSP75 (BSP613P) to BSP75N.
    - FDN 360P to FDN340P (logic level).
    - LP298SX to LP5907 (250 mA).
2018-03-01 Update ICs, change routes and power source.
    Changes made:
    - BSP75 (BSP613P) to BSP75N.
    - FDN 360P to FDN340P (logic level).
    - LP298SX to LP5907 (250 mA).
2018-04-26 Update ICs, change routes and power source.
    Changes made:
    - BSP75 (BSP613P) to BSP75N.
    - FDN 360P to FDN340P (logic level).
    - LP298SX to LP5907 (250 mA).
2018-04-26 Create documentation for Standard Transducer parameters.
2018-04-27 Update Arduino files.
2018-06-08 Create code for OLED over ChiNil RTOS
    Add libraries for work with OLED and Serial.
2018-06-09 Test serial communication and I2C in same time
    There is a problem with correct work for I2C and Serial.
2018-06-15 Update Serial Thread
    Add new options for Serial Thread.
2018-06-15 Update CONSTANTS
    Update STrans.h with new constants.
2018-06-18 Update Serial and create Parameters
    New configuration for Serial and creat a Parameters.
2018-06-19 Update Serial
    Create new functions for Flags into Serial file.
2018-06-20 Create new pressure Test
    Add new functions for STrans and create a Pressure Test.
2018-06-23 Solved communication between OLED and others threads
    Solved variables read in multiple threads and solved write and read EEPROM from differents threads
2018-06-28 Update documentation.
    Update parameter 22.
2018-06-28 Update documentation
2019-08-13 Update
    Update Doc/Readme .md

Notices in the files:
parts and their libraries:
lpatiny: ©2009 ROFA.cz - modified and updated by Robert Darlington ‹rdarlington@gmail.com›
SparkFun-Switches: Licensing: Creative Commons ShareAlike 4.0 International - https://creativecommons.org/licenses/by-sa/4.0
